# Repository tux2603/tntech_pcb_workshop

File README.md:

# tntech_pcb_workshop

Files and references for a PCB design workshop at Tennessee Tech. The workshop will focus on designing and assembling a two-layer PCB for a simple Arduino-compatible STM32 development board, and will serve as a first-introduction to PCB design and assembly for students. Students are expected to have a familiarity with basic electrical engineering concepts such as Ohm's law, impedance, and basic circuit analysis, but no prior experience with PCB design is required. The workshop will be hands-on, and will culminate in students assembling a (hopefully) functional PCB that they will be able to take home with them.

Additional information can be found in the [documentation](documentation/main.md) for the workshop. Slides shown in the workshop can be found in the [slides](documentation/slides/main.md) section of the documentation.

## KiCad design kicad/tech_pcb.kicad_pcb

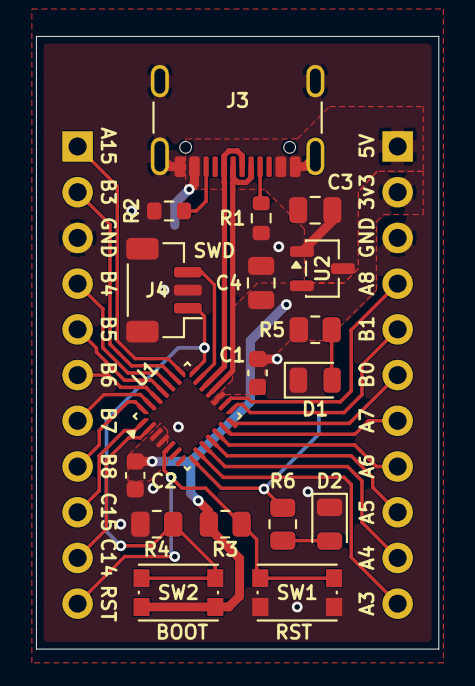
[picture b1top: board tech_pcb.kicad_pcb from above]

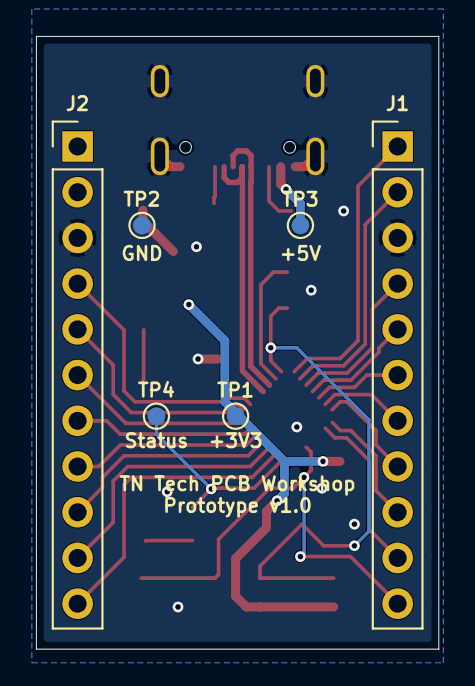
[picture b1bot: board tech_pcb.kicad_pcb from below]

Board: 2 copper layers, 22.4 x 34.0 mm, 24 parts (6 on the bottom side), 30 nets.

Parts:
C1, C2: 100n; C_0603_1608Metric
C3, C4: 1u; C_0805_2012Metric
D1: PWR; LED_0805_2012Metric
D2: STATUS; LED_0805_2012Metric
J1, J2: Conn_01x11; PinHeader_1x11_P2.54mm_Vertical
J3: USB_C_Receptacle_USB2.0_16P; USB_C_Receptacle_GCT_USB4105-xx-A_16P_TopMnt_Horizontal
J4: Conn_01x03_MountingPin; JST_SH_BM03B-SRSS-TB_1x03-1MP_P1.00mm_Vertical
R1, R2: 5k1; R_0603_1608Metric
R3, R4: 10k; R_0805_2012Metric
R5, R6: 220; R_0805_2012Metric
SW1: RST; SW_Push_1P1T_NO_CK_KMR2
SW2: BOOT; SW_Push_1P1T_NO_CK_KMR2
TP1, TP2, TP3, TP4: TestPoint; TestPoint_Pad_D1.0mm
U1: STM32C071GBUxN; QFN-28_4x4mm_P0.5mm
U2: XC6206PxxxMR; SOT-23-3

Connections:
+3V3: C1.1, C2.1, C4.1, J2.2, R3.1, R5.1, SW2.2, TP1.1 (1_1), U1.3 (VDD), U1.17 (VDDIO2), U2.2 (VO)
+5V: C3.1, J2.1, J3.A4 (VBUS), J3.A9 (VBUS), J3.B4 (VBUS), J3.B9 (VBUS), TP3.1 (1_1), U2.3 (VI)
/BOOT0: J4.1, R4.1, SW2.1, U1.21 (PA14)
/NRST: J1.11, R3.2, SW1.2, U1.5 (PF2)
/PA3: J2.11, U1.9 (PA3)
/PA4: J2.10, U1.10 (PA4)
/PA5: J2.9, U1.11 (PA5)
/PA6: J2.8, U1.12 (PA6)
/PA7: J2.7, U1.13 (PA7)
/PA8: J2.4, U1.16 (PA8)
/PA15: J1.1, U1.22 (PA15)
/PB0: J2.6, U1.14 (PB0)
/PB1: J2.5, U1.15 (PB1)
/PB3: J1.2, U1.23 (PB3)
/PB4: J1.4, U1.24 (PB4)
/PB5: J1.5, U1.25 (PB5)
/PB6: J1.6, U1.26 (PB6)
/PB7: J1.7, U1.27 (PB7)
/PB8: J1.8, U1.28 (PB8)
/PC14: J1.10, U1.2 (PC15)
/PC15: J1.9, U1.1 (PC14)
/STATUS: R6.1, TP4.1 (1_1), U1.8 (PA2)
/SWDIO: J4.3, U1.20 (PA13)
/USB_DN: J3.A7 (D-), J3.B7 (D-), U1.18 (PA11)
/USB_DP: J3.A6 (D+), J3.B6 (D+), U1.19 (PA12)
GND: C1.2, C2.2, C3.2, C4.2, D1.1 (K), D2.1 (K), J1.3, J2.3, J3.A1 (GND), J3.A12 (GND), J3.B1 (GND), J3.B12 (GND), J3.SH (SHIELD), J4.2, J4.MP (MountPin), R1.2, R2.2, R4.2, SW1.1, TP2.1 (1_1), U1.4 (VSS), U2.1 (GND)
unnamed: D1.2 (A), R5.2
unnamed: D2.2 (A), R6.2
unnamed: J3.A5 (CC1), R1.1
unnamed: J3.B5 (CC2), R2.1
